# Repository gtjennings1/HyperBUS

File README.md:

# HyperRAM
A basic HyperRAM controller for Lattice iCE40 Ultraplus FPGAs

You can download a Verilog model of the Cypress HyperRAM from their website.
http://www.cypress.com/verilog/s27kl0641-verilog

​	bitstream/	- Contains pre-synthesized and compiled FPGA bitstream and RISC-V firmware files

​	radiant/		- Lattice Radiant project of the RISC-V + HyperRAM controller design

​	iCEStorm/	- iCEStorm project of the RISC-V + HyperRAM controller design

​	riscv32/		- picorv32 and picoSoC RISC-V files

​	simulation/	- Simulation of standalone controller

​	standalone/	- Simple HyperRam Controller

Sources:
RISC-V examples were based off of the PicoSoC examples provided by mmicko at the Hackaday FPGA101 Workshop.  Thank you for the great examples mmicko!
https://github.com/mmicko/fpga101-workshop

## How do I use this project

This project provide examples for APIO and iCEStorm projects and also The Lattice Radiant sotware.

### Build and upload under iCEStorm 
1. Install iCEStorm (http://www.clifford.at/icestorm/)
2. Run the following commands
    cd ./icestorm
    ./hyperram.sh
    iceprog hyperram.bin

### Build and upload under APIO project
1. Install APIO (https://github.com/FPGAwars/apio)
2. Run the following commands
    cd ./riscv32/hardware
    apio build
    apio upload

### Build and upload under Radiant software
1. Install the Laticce Radiant software (http://www.latticesemi.com/Products/DesignSoftwareAndIP/FPGAandLDS/Radiant)
2. Open radiant/riscv32_radiant.rdf file
3. Build and upload the project using the Radiant Software

### Build and upload the software for RISCV32 
1. If you use the APIO project:
    cd ./riscv32/software
    apio make
    apio make upload

2. In other cases 
   riscv64-unknown-elf-gcc -O3 -nostartfiles -mabi=ilp32 -march=rv32ic -Wl,-Bstatic,-T,sections.lds,--strip-debug -ffreestanding -o firmware.elf start.s sections.c firmware.c -lgcc
   riscv64-unknown-elf-objcopy  -O binary firmware.elf firmware.bin

3. Upload firmware.bin
* iCEStorm:
    iceprog -o 1M firmware.bin
* Radiant: upload the firmware.bin file using the programmer tool. The start address should be 1MB (see readme.md in bitstream/)

## Project Description

FPGA Project contains a RISC-V core with the hyperram controller connected.  Write and read tests are performed on the memory.

- On power up, the RGB LED will light up red
  - This insures the FPGA bitstream is loaded properly and that the RISC-V code in SPI Flash is executing.

- Shortly after words the RGB LED will flash blue or green
  - Green = read/write tests are passing
  - Blue = read/write tests are failing

Additionally, there is a UART TX port on pin 36.  If you connect it to a terminal window you can monitor the tests.  You can use the Adafruit FT232H USB board for this and connect a fly wire between pin 38 on the UPDuino and D1 and a ground wire between both boards.  Set the baud rate to 9600.

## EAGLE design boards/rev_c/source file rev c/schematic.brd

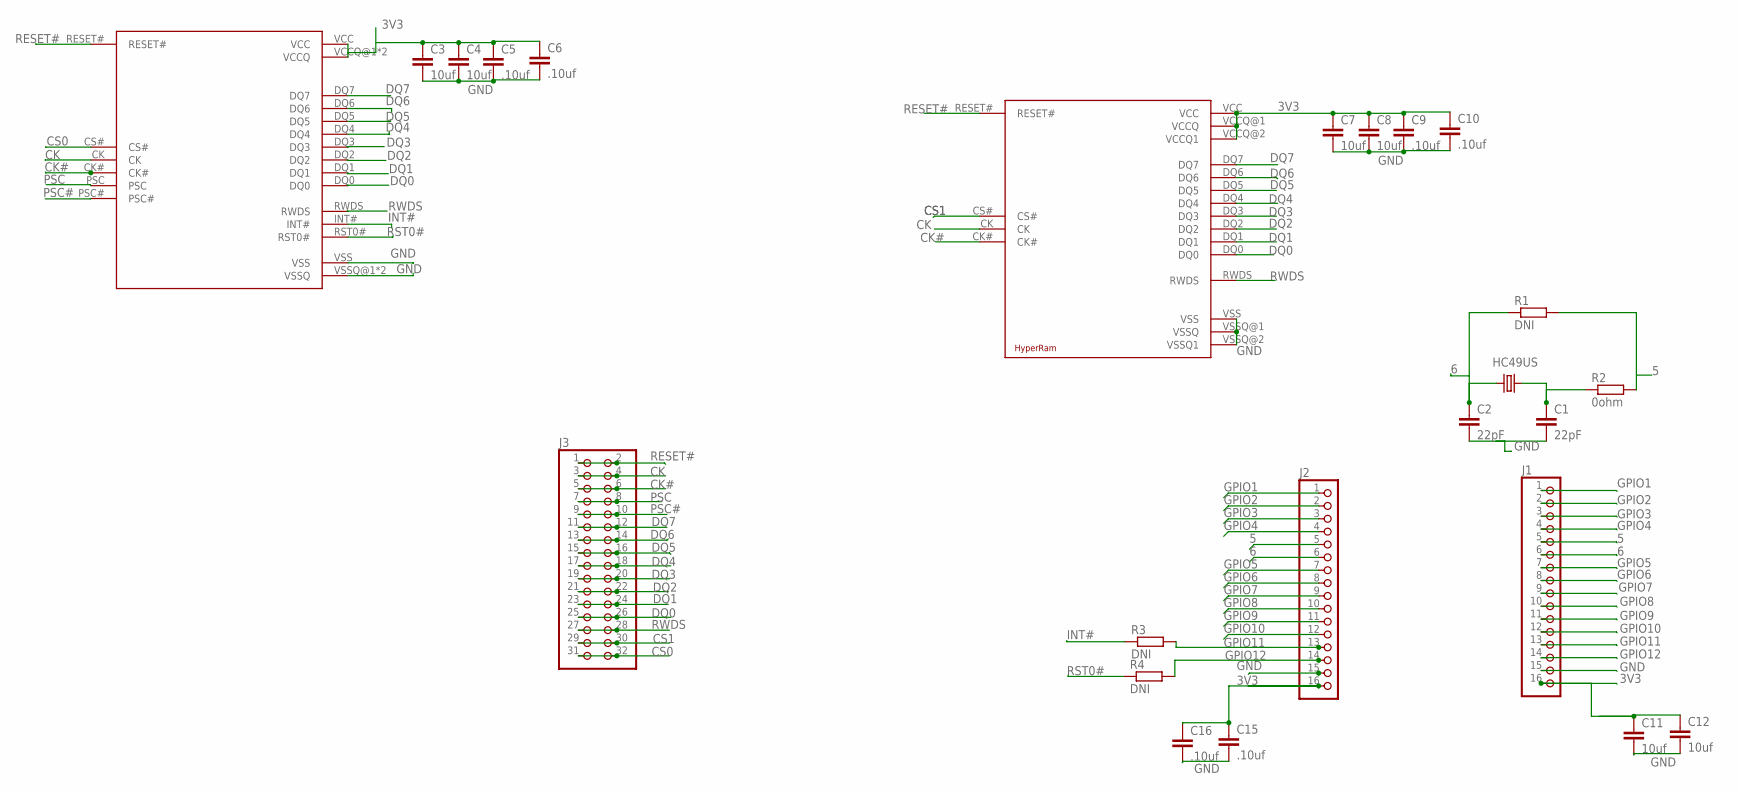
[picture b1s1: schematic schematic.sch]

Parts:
C1, C2: 22pF; C0603
C3, C4, C7, C8, C11, C12: 10uf; C0402
C5, C6, C9, C10, C15, C16: .10uf; C0402
HC49US: 12 Mhz; HC49UP
J1, J2: PINHD-1X16; 1X16
J3: PINHD-2X16; 2X16
R1, R3, R4: DNI; R0603
R2: 0ohm; R0603
U$1: HYPERFLASH_MEMORY; BGA-24
U$2: HYPERFLASH_MEMORY; BGA-24_RAM

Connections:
3V3: C3.1, C4.1, C5.1, C6.1, C7.1, C8.1, C9.1, C10.1, C11.1, C12.1, C15.1, C16.1, J1.16, J2.16, U$1.VCC, U$1.VCCQ@1 (VCCQ), U$1.VCCQ@2 (VCCQ), U$2.VCC, U$2.VCCQ@1 (VCCQ), U$2.VCCQ@2 (VCCQ1)
5: J1.5, J2.5, R1.2, R2.2
6: C2.1, HC49US.1, HC49US.P$1 (1), J1.6, J2.6, R1.1
CK: J3.3, J3.4, U$1.CK, U$2.CK
CK#: J3.5, J3.6, U$1.CK#, U$2.CK#
CS0: J3.31, J3.32, U$1.CS#
CS1: J3.29, J3.30, U$2.CS#
DQ0: J3.25, J3.26, U$1.DQ0, U$2.DQ0
DQ1: J3.23, J3.24, U$1.DQ1, U$2.DQ1
DQ2: J3.21, J3.22, U$1.DQ2, U$2.DQ2
DQ3: J3.19, J3.20, U$1.DQ3, U$2.DQ3
DQ4: J3.17, J3.18, U$1.DQ4, U$2.DQ4
DQ5: J3.15, J3.16, U$1.DQ5, U$2.DQ5
DQ6: J3.13, J3.14, U$1.DQ6, U$2.DQ6
DQ7: J3.11, J3.12, U$1.DQ7, U$2.DQ7
GND: C1.2, C2.2, C3.2, C4.2, C5.2, C6.2, C7.2, C8.2, C9.2, C10.2, C11.2, C12.2, C15.2, C16.2, J1.15, J2.15, U$1.VSS, U$1.VSSQ@1 (VSSQ), U$1.VSSQ@2 (VSSQ), U$2.VSS, U$2.VSSQ@1 (VSSQ), U$2.VSSQ@2 (VSSQ1)
GPIO1: J1.1, J2.1
GPIO2: J1.2, J2.2
GPIO3: J1.3, J2.3
GPIO4: J1.4, J2.4
GPIO5: J1.7, J2.7
GPIO6: J1.8, J2.8
GPIO7: J1.9, J2.9
GPIO8: J1.10, J2.10
GPIO9: J1.11, J2.11
GPIO10: J1.12, J2.12
GPIO11: J1.13, J2.13, R3.2
GPIO12: J1.14, J2.14, R4.2
INT#: R3.1, U$1.INT#
unnamed: C1.1, HC49US.2, HC49US.P$2 (2), R2.1
PSC: J3.7, J3.8, U$1.PSC
PSC#: J3.9, J3.10, U$1.PSC#
RESET#: J3.1, J3.2, U$1.RESET#, U$2.RESET#
RST0#: R4.1, U$1.RST0#
RWDS: J3.27, J3.28, U$1.RWDS, U$2.RWDS

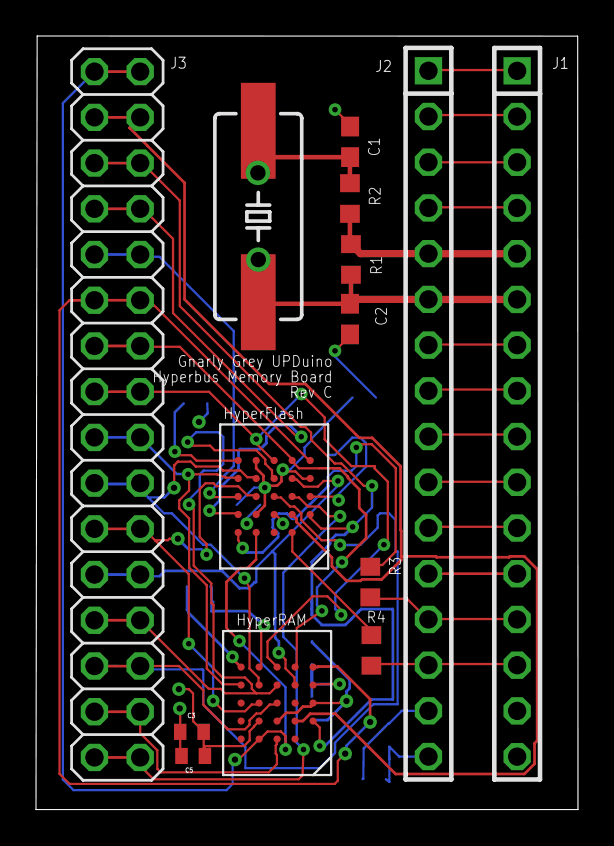
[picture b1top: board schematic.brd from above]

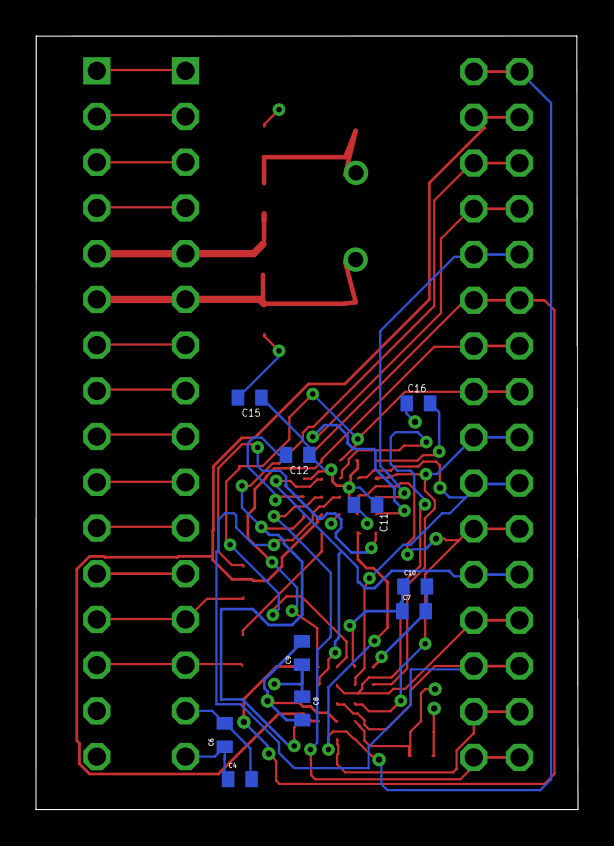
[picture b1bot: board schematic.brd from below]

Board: 4 copper layers, 30.1 x 43.0 mm, 24 parts (10 on the bottom side), 35 nets.

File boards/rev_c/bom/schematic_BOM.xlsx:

Qty | Value | Part Num | Package | Parts
 | DNI |  | 1X16 | J1, J2
 | DNI |  | 2X16 | J3
6 | .10uf |  | C0402 | C5, C6, C9, C10, C15, C16
1 | 0ohm |  | R0603 | R2
6 | 10uf |  | C0402 | C3, C4, C7, C8, C11, C12
 | DNI |  | HC49UP | HC49US
2 | 22pF |  | C0603 | C1, C2
3 | DNI |  | R0603 | R1, R3, R4
1 | DNI | S26KL128SDABHI030 | BGA-24 | U$1
1 | S27KL0641DABHV020 | S27KL0641DABHV020 | BGA-24 | U$2

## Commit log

2018-08-09 added standalone hbc
2018-08-10 added wrapper and testbench
2018-08-15 tesbench works
2018-08-16 added riscv32 project
2018-08-17 added the Radiant project
2018-08-24 added icestorm makefile
2018-08-24 added apio.ini
2018-08-25 added sources for icestorm/apio projects
2018-11-28 Added rev c board
2018-12-24 fixed icestorm project
2019-01-07 added firmware
2019-01-07 working bitstream and firmware and fixed issue with hyperram script
2019-01-07 adding binary combiner
2019-01-07 removed errors in combine.bin
2019-01-07 removed errors in combine.bin and bincombine.py
2019-01-07 added some information about the test project
2019-01-08 better timing
